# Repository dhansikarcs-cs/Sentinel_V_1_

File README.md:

# Sentinel — On-Premises Psychophysiological Triage Node

**Continuous mental health infrastructure connecting patients and clinicians through real-time monitoring, AI-powered journal analysis, crisis escalation, and structured follow-up management.**

> **Stack:** FastAPI + SQLAlchemy (SQLite/PostgreSQL) · React 19 + TypeScript + Vite · Ollama/Groq AI · PWA · Docker Compose · Nginx
> **Status:** Hardware M0 complete (ring SDK + device binding) · Emergent Ventures funded · OEM ring (Jport) in procurement

---

## What Sentinel Does

- **Continuous biometric ingestion** from smart rings (HR, HRV, stress) via a pluggable adapter SDK (`BLE` gateway, vendor cloud, or deterministic simulator)
- **Journal analysis** with AI summaries — a warm companion tone for the patient, a structured OAP clinical summary for the psychologist
- **Discrepancy engine** — rule-based, zero-ML classifier flagging mismatches between subjective journal text and objective physiology
- **Crisis engine** — deterministic escalation (patient → psychologist → trusted contact → helpline) with an active-crisis WebSocket broadcast
- **Clinical workspace** — triage, clinical notes, bookings, follow-up grading, export center
- **Security** — HttpOnly JWT + per-device ring tokens (SHA-256 at rest, constant-time compare), field-level encryption (Fernet), hash-chained audit log, rate limiting

---

## Architecture

```
OEM ring ─┬─ BLE gateway (bleak) ─┐
          ├─ vendor cloud SDK ────┤→ RingSource adapters → SensorData → POST /ring/data
          └─ simulated (dev/test) ┘                                    │
                                                     get_ring_identity (device token)
                                                                      ↓
Frontend (PWA) ── Nginx ── FastAPI API ── SQLite/PostgreSQL
                       │        └─ Ollama (local) → Groq (cloud) → rule fallback
                       └─ WebSocket (crisis broadcast)
```

```
sentinel3/
├── backend/
│   ├── app/
│   │   ├── main.py                    # FastAPI entry point, middleware, routers
│   │   ├── api/                       # Routers: auth, journal, crisis, ring, triage, ...
│   │   ├── core/                      # Config, DB, security, rate limiting, dependencies
│   │   ├── models/                    # SQLAlchemy models (users, journal, ring_device, ...)
│   │   ├── schemas/                   # Pydantic request/response schemas
│   │   ├── services/                  # audit, websocket, search
│   │   │   └── ring/                  # RingSource SDK: base, simulated, ble_gatt, vendor_api
│   │   ├── ml/                        # emotion_classifier, risk_engine, model_registry
│   │   ├── events/                    # Event subscribers (audit trail, event store)
│   │   ├── workers/                   # AI background worker
│   │   └── repositories/              # Data-access layer
│   ├── benchmarks/                    # IRIS-style benchmark suite
│   ├── alembic/                       # DB migrations
│   └── requirements*.txt
├── frontend/                          # React 19 + TypeScript + Vite + Tailwind (PWA)
│   └── src/{api,components,lib,pages,stores}
├── scripts/                           # ring_bridge, sim_ring, test_ring_api, seeding, ML training
├── docs/                              # Design, decisions, judge Q&A, hardware roadmap
├── docker-compose.yml
└── README.md
```

---

## Hardware Ingestion (M0)

| Component | What it does |
|-----------|--------------|
| `POST /ring/pair` | Binds a device serial to the patient, issues a one-time device token |
| `POST /ring/unpair` | Revokes a device; re-pairing issues a fresh token |
| `POST /ring/data` | Authenticated push (device token or patient JWT) → canonical `SensorData` |
| `GET /ring/devices` | Device state for patient or psychologist |
| `RingSource` SDK | `SimulatedRing` (deterministic per-user/hour), `VendorAPIRingSource` (cloud SDK), `BLEGATTRingSource` (bleak, HRM 0x2A37 + battery 0x180F) |
| `scripts/ring_bridge.py` | Polls any adapter and pushes through the authenticated path |
| `scripts/sim_ring.py` | Streams simulated device-token data (`--once` for a single push) |

Tokens are stored as SHA-256 hashes, compared with `hmac.compare_digest`, and honored per-request. See `docs/ROADMAP_HARDWARE.md` for the M1–M3 plan.

---

## Quick Start

### Backend

```bash
cd backend
python -m venv venv
venv\Scripts\activate
pip install -r requirements.txt
pip install -r requirements-bridge.txt   # only needed for BLE ring bridge
python seed_demo.py                        # seed demo accounts
uvicorn app.main:app --reload --port 8000
```

Health check: `http://localhost:8000/health`

### Frontend

```bash
cd frontend
npm install
npm run dev
```

### Full stack (Docker)

```bash
docker compose up --build
```

---

## Testing

```bash
python scripts/test_ring_api.py    # 9 ring SDK/API tests (incl. BLE parsers)
cd backend && python -m pytest     # backend test suite
```

---

## Accounts (demo seed)

| Role | Username | Notes |
|------|----------|-------|
| Patient | `cel` | `123456` |
| Psychologist | `alaya` | `654321` |
| Demo ring | `RING-DEMO-001` | paired to `alaya` (device token via `/ring/pair`) |

---

## Data Privacy & Security

- Journal raw content encrypted at rest (Fernet, key derived via PBKDF2 600K + HKDF)
- Ring tokens hashed at rest, constant-time comparison, per-request revocation
- HttpOnly cookie JWT (8h) + localStorage fallback for programmatic clients
- Hash-chained audit log; rate limiting (100 req/min/IP); internal Docker network; sanitized 500s
- `.env` holds secrets — excluded from version control

---

## Documentation

| Doc | Purpose |
|-----|---------|
| `docs/TECHNICAL_DESIGN.md` | Full architecture, decisions, trade-offs |
| `docs/ENGINEERING_DECISIONS.md` | Every key decision and alternative |
| `docs/ENGINEERING_LOGBOOK.md` | Build narrative with timestamps |
| `docs/JUDGE_QA.md` | Anticipated judge questions + defensible answers |
| `docs/ROADMAP_HARDWARE.md` | Hardware milestones M1–M3 |
| `docs/sentinel_paper.md` / `.pdf` | Research paper (markdown source + PDF build via `scripts/generate_paper_pdf.py`) |
| `SENTINEL_CODEBOOK.md` | Per-file code explanation |

---

## License

Educational project. Built for demonstration of a full-stack healthcare simulation platform.

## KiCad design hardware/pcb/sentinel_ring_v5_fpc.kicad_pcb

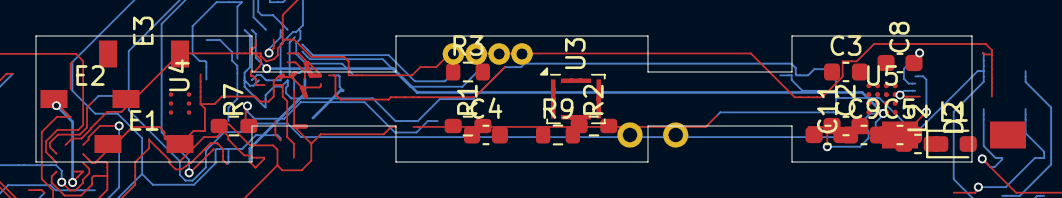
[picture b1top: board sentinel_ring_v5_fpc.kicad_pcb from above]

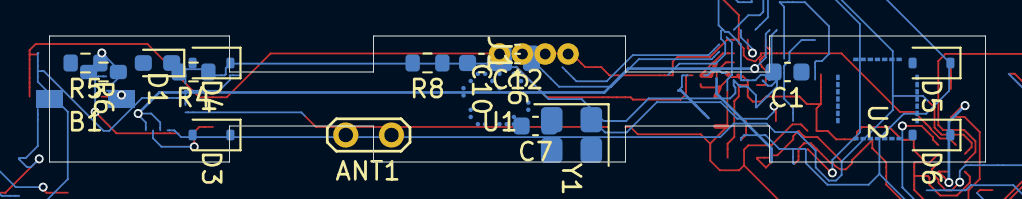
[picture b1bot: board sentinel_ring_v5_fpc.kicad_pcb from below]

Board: 2 copper layers, 52.0 x 7.0 mm, 41 parts (20 on the bottom side), 29 nets.

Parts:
ANT1: ANT; TestPoint_Pad_D1.0mm
B1: Li-Po Curved; Battery_Connector
C1, C4, C8: 100nF; C_0603_1608Metric
C2, C5: 10uF; C_0603_1608Metric
C3, C9, C11: 1uF; C_0603_1608Metric
C6, C7: 12pF; C_0603_1608Metric
C10: 4.7uF; C_0603_1608Metric
C12: 1.5pF; C_0603_1608Metric
D1: Green; LED_0603_1608Metric
D2: Red; LED_0603_1608Metric
D3, D4, D5, D6: BAT54; D_SOD-323
E1: ECG Electrode R; ECG_Electrode
E2: ECG Electrode L; ECG_Electrode
E3: EDA Electrode; ECG_Electrode
J1: TestHeader_1x04_P1.27mm; PinHeader_1x04_P2.54mm
L1: Charging Coil; Coil_Charging
L2: 2.2uH; L_0603_1608Metric
R1, R2, R3: 4k7; R_0603_1608Metric
R4, R7: 10k; R_0603_1608Metric
R5, R6: 330; R_0603_1608Metric
R8: 1M5; R_0603_1608Metric
R9: 1M; R_0603_1608Metric
U1: nRF5340-CLAA-R; nRF5340_CLAA_R
U2: MAX86178; MAX86178_OLGA28
U3: BMI270; Bosch_LGA-14_3x2.5mm_P0.5mm
U4: AS6223; AS6223_WLCSP6
U5: BQ25180; BQ25180_WCSP16
Y1: 32MHz; Crystal_SMD_3225-4Pin_3.2x2.5mm

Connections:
/LED_G_A: D1.2, R5.1
/LED_R_A: D2.2, R6.1
BAT_MON: R8.2, R9.1, U1.19
CHG_STAT: D1.1, U5.C2
COIL_N: D4.1, D6.2, L1.2
COIL_P: D3.2, D5.1, L1.1
ECG_N: E2.1, U2.19
ECG_P: E1.1, U2.18
EDA_P: E3.1, U2.20
GND: C1.2, C2.2, C3.2, C4.2, C5.2, C6.2, C7.2, C8.2, C9.2, C10.2, C11.2, C12.2, D4.2, D5.2, E1.2, E2.2, E3.2, J1.4, R4.2, R7.2, R9.2, U1.5, U1.6, U1.7, U2.4, U2.5, U2.6, U3.1, U3.2, U3.8, U3.11, U3.12, U3.14, U4.4, U4.6, U5.D3
I2C_SCL: R3.2, U1.14, U2.8, U3.6, U4.1, U5.C4
I2C_SDA: R2.2, U1.13, U2.7, U3.5, U4.2, U5.B4
INT_BIO: U1.20, U2.9, U2.11
INT_IMU: U1.15, U3.9
INT_TEMP: U1.16, U4.5
ISET: R4.1, U5.D1
PMID: C8.1, C9.1, U5.A1, U5.A2
PWR_FLAG: B1.1, B1.2, U5.B1
PWR_GD: D2.1, U5.C3
REXT: R7.1, U2.10
RF_ANT: ANT1.1, C12.1, U1.8
SWDCLK: J1.3, U1.12
SWDIO: J1.2, U1.11
SW_NODE: L2.1, U5.A3
VBAT: C1.1, C2.1, C3.1, C4.1, C5.1, C10.1, J1.1, L2.2, R1.1, R1.2, R2.1, R3.1, R5.2, R6.2, R8.1, U1.1, U1.2, U1.3, U1.4, U2.1, U2.2, U2.3, U3.3, U3.4, U3.7, U4.3, U5.A4, U5.C1
VBUS: D3.1, D6.1
VDD_REF: C11.1, U5.B3
XL1: C6.1, U1.9, Y1.1
XL2: C7.1, U1.10, Y1.2

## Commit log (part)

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2026-05-12 initial commit — Sentinel mental health platform
2026-05-12 add streamlit-autorefresh to requirements
2026-05-12 add streamlit-autorefresh dep
2026-05-12 remove .venv from repo
2026-05-12 fix Groq logging, encryption key for cloud
2026-06-09 Initial commit: Sentinel V1 ecosystem - patient/psych portals, crisis detection, ring pipeline, AI agents, activity feed, priority triage, onboarding
2026-06-15 fix(booking): prevent calendar toggle bug when re-selecting dates
    All available dates render as Streamlit buttons (primary=selected,
    secondary=unselected) instead of switching between div/button, so clicking
    28→21→28 works normally instead of undoing 21 first.
2026-06-15 ui: polish spacing, shapes, segmented control, hover effects
2026-06-15 ui: calm dusk-slate palette based on color theory
    Replace harsh near-black bg (#0f1525) with warm deep slate
    (#171c2a→#1b2132→#161b28). Blues shifted warmer (#5b9cf5).
    All surfaces, borders, text, and inputs recalibrated to
    muted professional palette that feels grounded not oppressive.
2026-06-16 ui: full palette shift to warm rose-mauve family for empathy
    Color theory rationale:
    - Warm muted rose (#c49ea4) as sole accent — associated with
    compassion, emotional safety, and connection
    - Deep warm slate bg (#161926→#1a1e2e→#151824) grounds without
    the coldness of near-black
    - All surfaces, borders, text, and controls unified in the same
2026-06-16 ui: purge all blue tones, full warm rose-mauve palette
    - Replaced all #60a5fa, #3b82f6, #a78bfa, #7a8aaa, #5a6a8a,
    #1a2238, #1e3a5a, #1e2940, #9aa8c0, #6bcbff, #c97bff,
    #1a3050, #0a2a1a, #7c3aed, #1a2a4a with warm equivalents
    - Every blue-gray, cold blue, or purple-blue tone now mapped
    to rose-mauve (#c49ea4), warm violet-slate (#1e2336), muted
    warm gray (#6a6474), or light rose (#d8b4ba)
2026-06-16 tests: fix 4 agent tests for AI-vs-rule tolerance
2026-06-16 ui: replace patient date-picker calendar with dropdown
    Removes the full calendar grid (month nav, day buttons, weekday
    headers) from patient booking. Patients now pick an available date
    from a simple dropdown of sorted future dates. Psychologist's own
    calendar for managing availability is untouched.
2026-06-16 fix: mood per-day lock + journal save reliability
    - Adds mood_log table (SQLite + PG schema) to persist daily mood
    - save_mood() / get_today_mood() upsert by patient+date
    - Mood emoji bar locks after first click for the day, resets next day
    - Removes st.rerun() after journal save so success message persists
    - Adds clear_on_submit=True so form clears after save
2026-06-16 fix: keep emoji buttons visible when mood is locked
    Instead of replacing buttons with text, keep all 5 emoji slots
    visible at all times. When locked: selected emoji highlighted,
    others dimmed, all non-interactive. When unlocked: all clickable.
2026-06-19 feat: onboarding flow, assigned psychs, emotion classifier, training pipeline
    - Added onboarding_step, contact_info, assigned_psych to patient_profiles
    - get_assigned_patients / get_clinic_psychs_for_registration for psych assignment
    - Registration now requires selecting a psychologist from the clinic
    - Clinic codes are reusable (not one-time)
    - All 20 test patients seeded under CLINIC_ALPHA with rotating psych assignment
    - emotion_classifier.py: TF-IDF + LogisticRegression over GoEmotions 28 labels
2026-06-20 docs: update README, CODEBOOK, INSTALL to reflect v3 architecture
    README: SQLite schema, rose-mauve palette, cel/alaya accounts,
    custom sentinel model, emotion classifier, 15 DB tables, project layout
    CODEBOOK: Complete rewrite — JSON→SQLite migration, mood lock flow,
    patient/clinical AI modes, echo detection, emotion classifier integration,
    palette reference, account system, registration flow
    INSTALL: Updated demo credentials, test account reference, sentinel model
2026-06-20 docs: add updated proposals (250/500/1000 words) reflecting v3
    - Replaced Mistral -> custom sentinel model (7.2B, therapy-tuned)
    - Replaced JSON storage -> SQLite/PostgreSQL dual backend (15 tables)
    - Added emotion classifier (GoEmotions 28 labels, TF-IDF pipeline)
    - Added dual-mode AI (patient reflection vs clinical OAP)
    - Added mood per-day lock with auto reset
    - Added rose-mauve palette, test suite (112 tests), PBKDF2 auth
2026-06-20 feat: mood timeline chart + risk badge + UI upgrade
    - get_mood_history() in data_manager_.py — returns last N days mood data
    - Patient journal: mini mood trend chart (7-day spline, colored by mood)
    - Psych triage: per-patient mood chart + warning badge when last 3
    entries are Sad/Down (consecutive low mood streak)
    - Plotly integration for both views with rose-mauve accent
2026-06-20 fix: correct passwords in docs (cel/123456, alaya/654321)
